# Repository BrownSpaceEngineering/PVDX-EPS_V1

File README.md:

# EPS_V1

Electrical Power System (EPS) for PVDX — battery charging, regulation, and power distribution.

## Status
- Design phase: layout
- Current rev: rev-1.3
- Contributors: Kelly Lin, Natalie Cavallo, Jayla Hsiung, Nick Cavallo, Emily Zhang, Dean Zweiman

## System overview

Four 2S battery packs (8x Tenergy 30005-0 18650 cells) feed a charge/regulation chain built entirely from dedicated power-management ICs, with no onboard MCU — charging, cell balancing, and telemetry are handled in hardware and reported to the compute board over I2C.

**Board sheets:**

- **Battery Pack 1–4**: one **MP2672AGD-0000-Z** charger per pack handles charging, discharging, and cell balancing without needing a microcontroller to manage the process. One **MAX17205** fuel gauge per pack reports state-of-charge and battery telemetry to the compute board over its own I2C pair (SDA/SCL), so each of the 4 packs has an independent data channel — a single fuel-gauge/charger failure doesn't take down monitoring for the other packs.
- **Charging Inputs**: the **MP28167GQ-Z** converts solar input down to a fixed 5V for charging. A **TPS2121RUXR** power mux sits between the solar and external-5V inputs and picks whichever is present, prioritizing external input — this is what lets the board charge normally on the bench (external 5V) without needing solar illumination, while still working correctly on orbit.
- **Converters**: three fixed-output regulators step the ~6–8.4V battery bus down to the rails other subsystems actually need: **TPS62133RGTR** (5V), **TPS62132RGTR** (3.3V), and **TPS61088RHLR** (12V boost, needed since 12V is above the battery bus voltage).
- **Connectors**: battery pack I/O, the RBF (remove-before-flight) pin, inhibit switches (mechanically disconnect batteries from load/ground when pressed — a safety requirement, not just a connector), and the ALRT signal and I2C breakout to the compute board.

### Repo layout

```
EPS_V1/
├── EPS_V1.kicad_pro / .kicad_sch / .kicad_pcb / .step
├── fp-lib-table, sym-lib-table
├── schematics/          # sub-sheets
├── libs/
│   ├── footprints.pretty/
│   ├── symbols/
│   └── 3dmodels/
├── spice/
│   ├── sims/
│   └── models/
├── tools/                # SPICE model translator script
└── manufacturing/
    └── rev-<N>_<date>/
        ├── gerbers/
        ├── bom/
        └── plots/
```

**Why 2S battery packs specifically:** 4x 2S (8 cells total) rather than one large pack — this is a mechanical/electrical packing choice under the ISS 80 Wh limit, and it gives pack-level redundancy (a single pack failure doesn't take down the whole EPS). It also matters electrically: a 2S pack has a ~6.0V floor, which the buck converters can cleanly step down to 5V and 3.3V — a single-cell pack's ~3.0V floor wouldn't support that.

## Key design notes

- **Charge voltage 4.2V, typical 3.6V, overdischarge floor raised from the cell's rated 2.75V to 3.0V** — added margin above the cell's absolute minimum.
- **MP2672A output current is being restricted below the MP28167GQ-Z's 3A capability** to stay under the board's actual current requirement (2.52A = 14/5×0.9). Open question below on whether that restriction should assume all 4 packs charging at once.
- **MAX17205's external-thermistor input is intentionally unused** — flight software reads temperature from the analog thermistor connection straight to the compute board instead, not through the fuel gauge.
- **TPS61088 (12V) key values:** 200kHz min switching frequency (840k resistor), 3A current limit (400k), PFM mode (MODE pin floating), R1 502k / R2 56k for 12V output, 2.2µH inductor per TI's recommended table.
- **Thermistor (NXFT15XV103FEAB025):** system draws 0.574mW through it against a 3mW rating — comfortable margin. Rated -40°C to 125°C.

## Simulations
- `spice/sims/` — EPS_U6, U2_EPS, U3_EPS, U6_EPS (regulator sims)
- `spice/models/` — TI PSpice models for TPS61088/TPS62132/TPS62133, both original and LTSpice-collapsed versions
- `tools/` — script + requirements to collapse TI's multi-line `.lib` continuation format into something LTSpice's autogenerator can parse

## Manufacturing history
| Rev | Date | Notes | Location |
|-----|------|-------|----------|
| 1.0 | 5/15/26 | First layout pass | `manufacturing/rev-1.0_2026-05-15/` |
| 1.2 | 8/7/26  | Prepared for schematic submittal | `manufacturing/rev-1.2_2026-08-07/` |
| 1.3 | 8/30/26  | Prepared for fabrication | `manufacturing/rev-1.3_2026-08-30/` |

## Open items / TBD
- S-band kill switch, FSW-configurable — not yet in design
- R_MID value for MP2672A — placeholder 0, needs datasheet-confirmed value (50Ω noted elsewhere from the fuel gauge datasheet — worth reconciling)
- Solar input voltage range (2.8–22V accepted) vs. actual solar board output — needs confirmation
- MP2672A max charge current restriction — should this account for a scenario where one pack is offline/broken?

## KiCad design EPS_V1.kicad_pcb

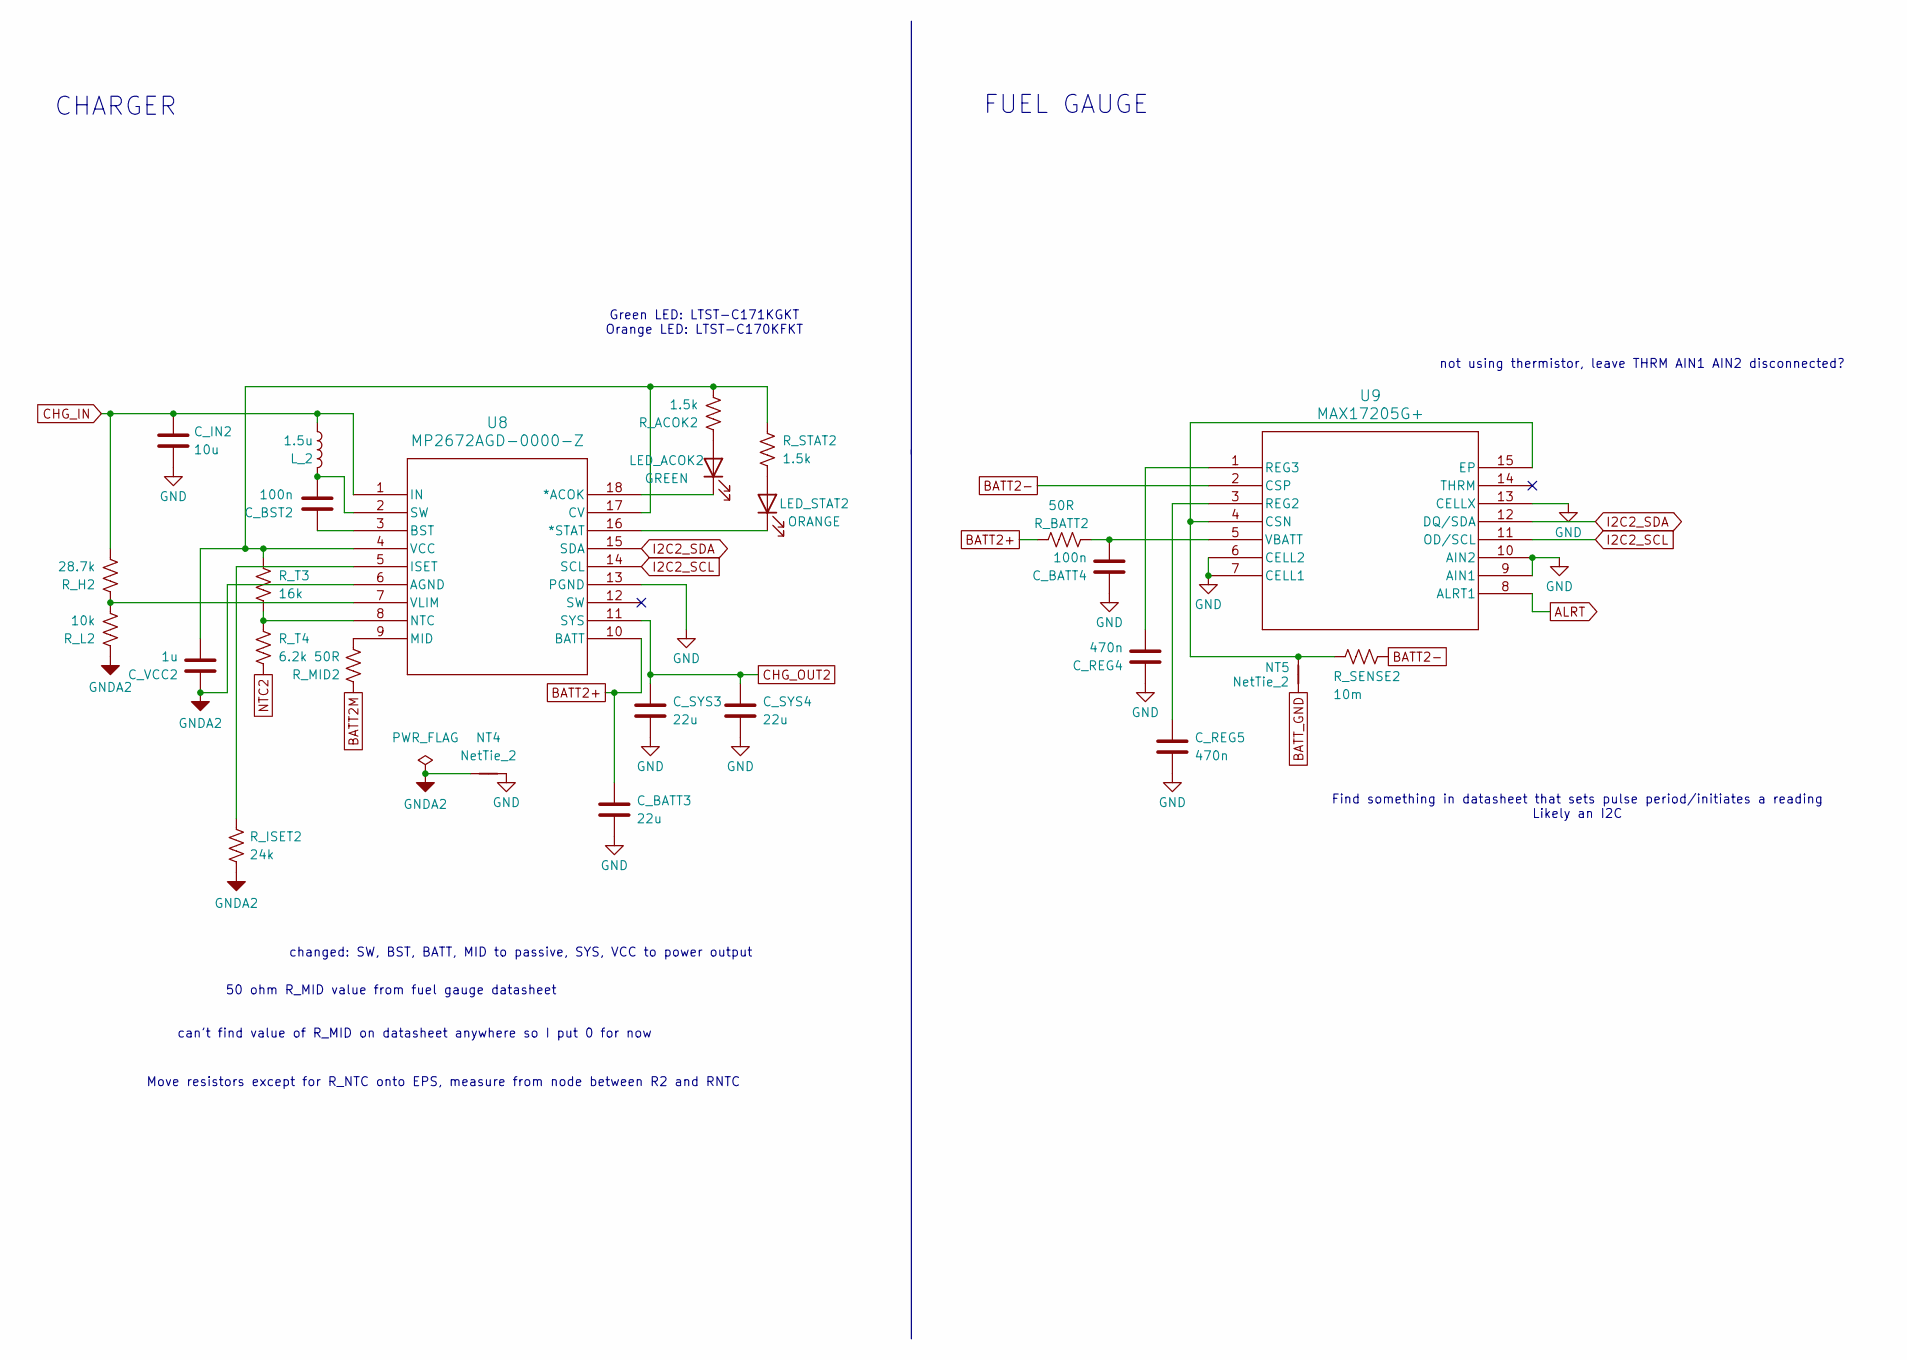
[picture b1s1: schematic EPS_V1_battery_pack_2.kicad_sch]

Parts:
C_BATT3: 22u; C_0805_2012Metric; Voltage Rating 25V
C_BATT4: 100n; C_0603_1608Metric; Voltage Rating 16V
C_BST2: 100n; C_0603_1608Metric; Voltage Rating 16V
C_IN2: 10u; C_0805_2012Metric; Voltage Rating 25V
C_REG4, C_REG5: 470n; C_0603_1608Metric; Voltage Rating 16V
C_SYS3, C_SYS4: 22u; C_0805_2012Metric; Voltage Rating 25V
C_VCC2: 1u; C_0603_1608Metric; Voltage Rating 16V
LED_ACOK2: GREEN; LED_0805_2012Metric; MPN LTST-C171KGKT
LED_STAT2: ORANGE; LED_0805_2012Metric; MPN LTST-C170KFKT
L_2: 1.5u; IND_AMELA2012S-1R5MT; MPN AMELA2012S-1R5MT
NT4, NT5: NetTie_2; NetTie-2_SMD_Pad0.5mm
R_ACOK2: 1.5k; R_0603_1608Metric
R_BATT2: 50R; R_0603_1608Metric
R_H2: 28.7k; R_0603_1608Metric
R_ISET2: 24k; R_0603_1608Metric
R_L2: 10k; R_0603_1608Metric
R_MID2: 50R; R_0603_1608Metric
R_SENSE2: 10m; R_0603_1608Metric
R_STAT2: 1.5k; R_0603_1608Metric
R_T3: 16k; R_0603_1608Metric
R_T4: 6.2k; R_0603_1608Metric
U8: MP2672AGD-0000-Z; QFN-18_MP2672A_MNP
U9: MAX17205G+; 21-0137_T1433&plus_2C_MXM

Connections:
ALRT: U9.8 (ALRT1); also elsewhere on the board
BATT2+: C_BATT3.1, R_BATT2.1, U8.10 (BATT); also elsewhere on the board
BATT2-: R_SENSE2.1, U9.2 (CSP); also elsewhere on the board
BATT2M: R_MID2.1; also elsewhere on the board
BATT_GND: NT5.1; also elsewhere on the board
CHG_IN: C_IN2.1, L_2.1, R_H2.2, U8.1 (IN); also elsewhere on the board
CHG_OUT2: C_SYS3.1, C_SYS4.1, U8.11 (SYS); also elsewhere on the board
GND: C_BATT3.2, C_BATT4.1, C_IN2.2, C_REG4.1, C_REG5.2, C_SYS3.2, C_SYS4.2, NT4.2, U8.13 (PGND), U9.6 (CELL2), U9.7 (CELL1), U9.9 (AIN1), U9.10 (AIN2), U9.13 (CELLX); also elsewhere on the board
GNDA2: C_VCC2.1, NT4.1, R_ISET2.2, R_L2.1, U8.6 (AGND)
I2C2_SCL: U8.14 (SCL), U9.11 (OD/SCL); also elsewhere on the board
I2C2_SDA: U8.15 (SDA), U9.12 (DQ/SDA); also elsewhere on the board
NTC2: R_T4.2; also elsewhere on the board
unnamed: C_BST2.2, L_2.2, U8.2 (SW)
unnamed: LED_ACOK2.2 (A), R_ACOK2.1
unnamed: LED_ACOK2.1 (K), U8.18 (*ACOK)
unnamed: LED_STAT2.2 (A), R_STAT2.2
unnamed: LED_STAT2.1 (K), U8.16 (*STAT)
unnamed: C_BST2.1, U8.3 (BST)
unnamed: C_VCC2.2, R_ACOK2.2, R_STAT2.1, R_T3.1, U8.4 (VCC), U8.17 (CV)
unnamed: R_ISET2.1, U8.5 (ISET)
unnamed: R_MID2.2, U8.9 (MID)
unnamed: R_T3.2, R_T4.1, U8.8 (NTC)
unnamed: R_H2.1, R_L2.2, U8.7 (VLIM)
unnamed: NT5.2, R_SENSE2.2, U9.4 (CSN), U9.15 (EP)
unnamed: C_REG5.1, U9.3 (REG2)
unnamed: C_REG4.2, U9.1 (REG3)
unnamed: C_BATT4.2, R_BATT2.2, U9.5 (VBATT)

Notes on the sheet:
Find something in datasheet that sets pulse period/initiates a reading Likely an I2C
CHARGER
Move resistors except for R_NTC onto EPS, measure from node between R2 and RNTC
50 ohm R_MID value from fuel gauge datasheet
FUEL GAUGE
not using thermistor, leave THRM AIN1 AIN2 disconnected?
can't find value of R_MID on datasheet anywhere so I put 0 for now
Green LED: LTST-C171KGKT Orange LED: LTST-C170KFKT
changed: SW, BST, BATT, MID to passive, SYS, VCC to power output

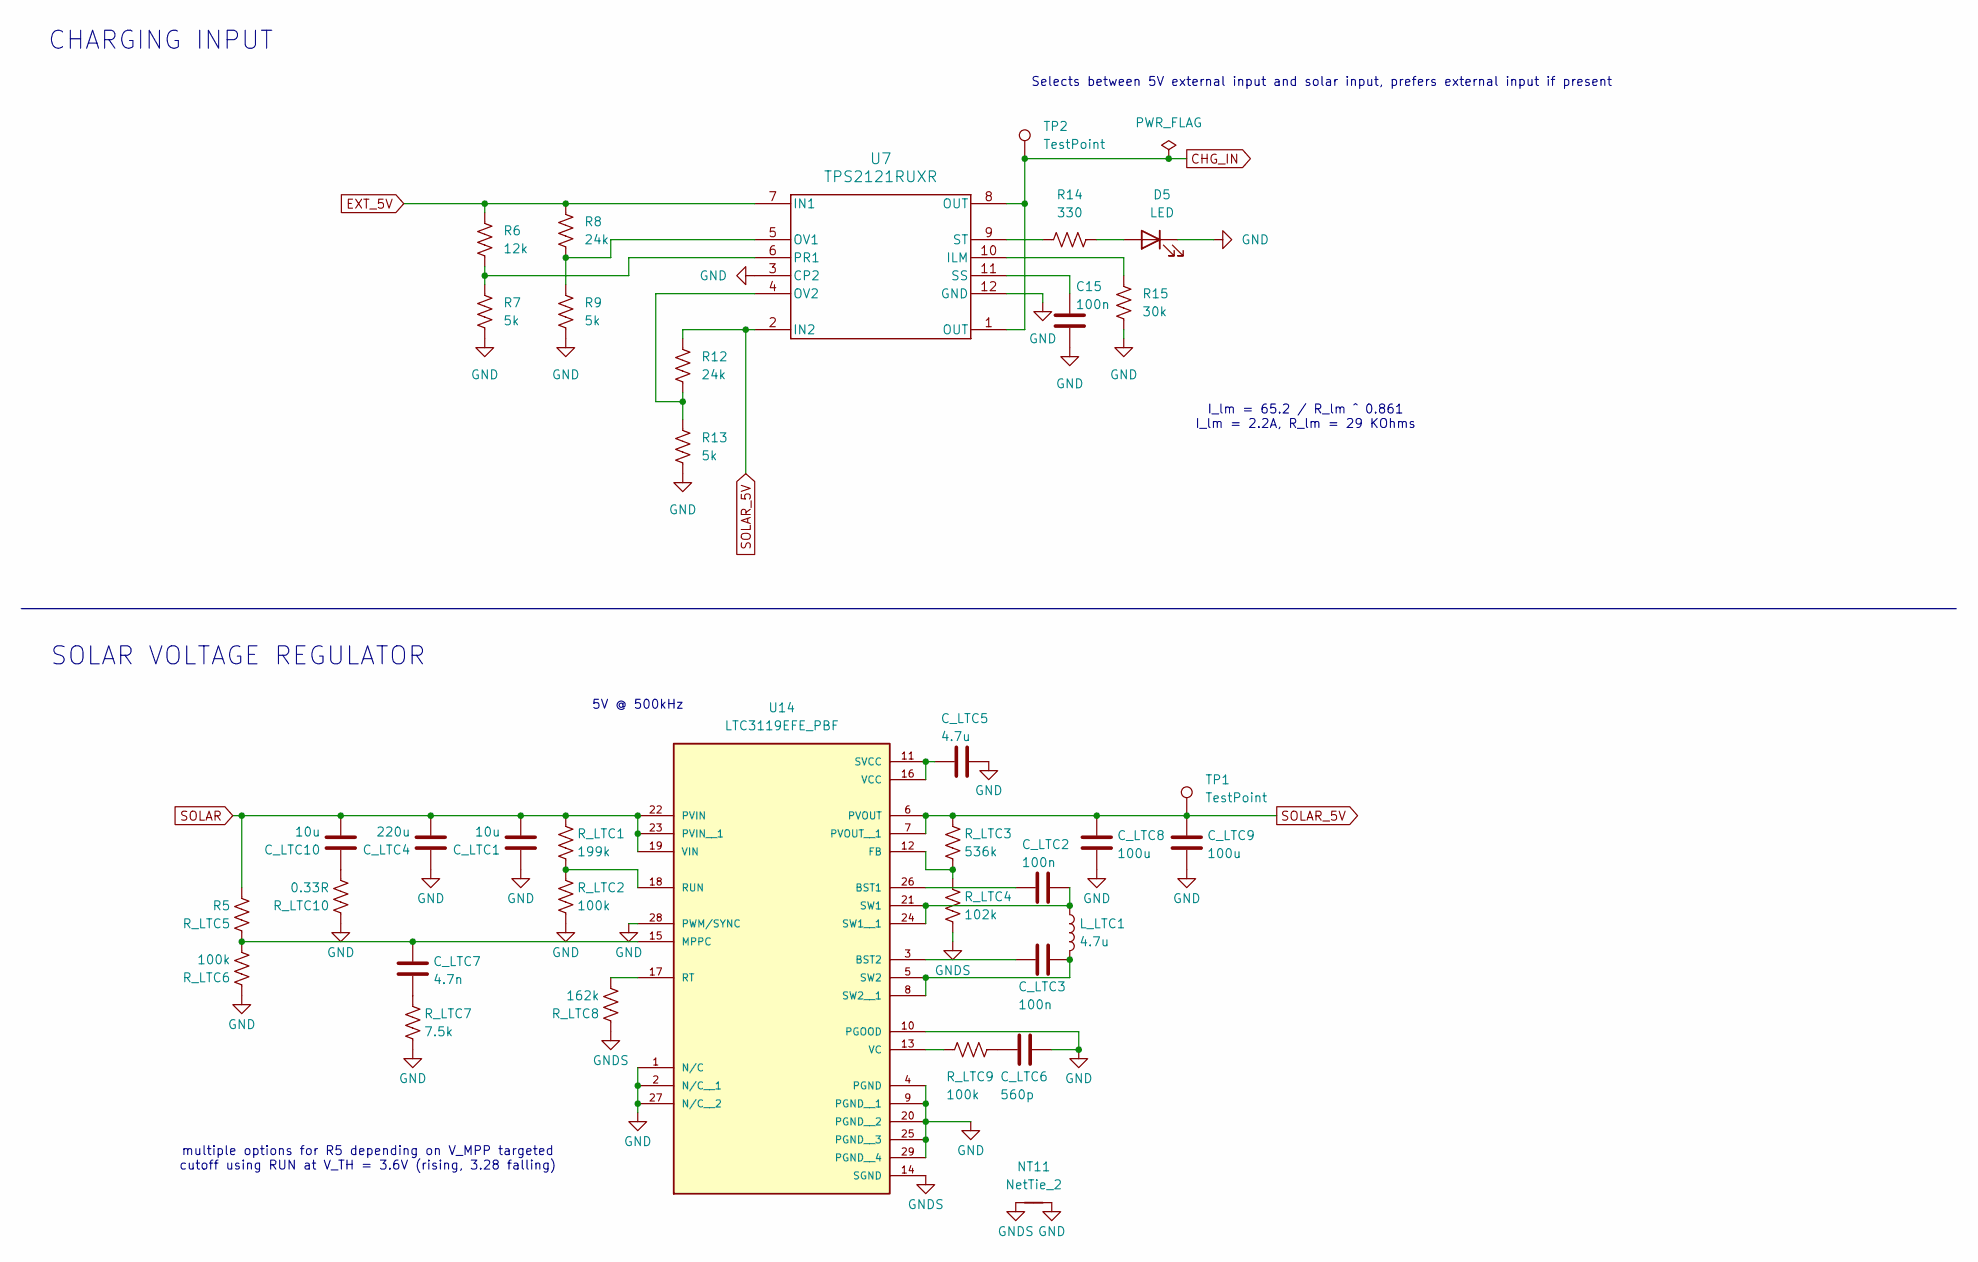
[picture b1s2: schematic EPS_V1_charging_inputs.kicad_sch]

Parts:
C15: 100n; C_0603_1608Metric
C_LTC1, C_LTC10: 10u; C_0805_2012Metric
C_LTC2, C_LTC3: 100n; C_0603_1608Metric
C_LTC4: 220u; CAPMP7.6X4.3_4.3N_KEM
C_LTC5: 4.7u; C_0603_1608Metric
C_LTC6: 560p; C_0603_1608Metric
C_LTC7: 4.7n; C_0603_1608Metric
C_LTC8, C_LTC9: 100u; C_1210_3225Metric
D5: LED; LED_0805_2012Metric
L_LTC1: 4.7u; IND_ASPI-7318-4R7M-T
NT11: NetTie_2; NetTie-2_SMD_Pad0.5mm
R6: 12k; R_0603_1608Metric
R7, R9, R13: 5k; R_0603_1608Metric
R8, R12: 24k; R_0603_1608Metric
R14: 330; R_0603_1608Metric
R15: 30k; R_0603_1608Metric
R_LTC1: 199k; R_0603_1608Metric
R_LTC2, R_LTC6, R_LTC9: 100k; R_0603_1608Metric
R_LTC3: 536k; R_0603_1608Metric
R_LTC4: 102k; R_0603_1608Metric
R_LTC5: R5; R_0603_1608Metric
R_LTC7: 7.5k; R_0603_1608Metric
R_LTC8: 162k; R_0603_1608Metric
R_LTC10: 0.33R; R_0603_1608Metric
TP1, TP2: TestPoint; TestPoint_Pad_D1.5mm
U7: TPS2121RUXR; RUX0012A
U14: LTC3119EFE_PBF; SOP65P640X120-29N; PARTREV B

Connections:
CHG_IN: TP2.1 (1_1), U7.1 (OUT), U7.8 (OUT); also elsewhere on the board
EXT_5V: R6.2, R8.2, U7.7 (IN1); also elsewhere on the board
GND: C15.2, C_LTC1.2, C_LTC4.2, C_LTC5.1, C_LTC6.1, C_LTC8.1, C_LTC9.1, D5.1 (K), NT11.2, R7.1, R9.1, R13.1, R15.1, R_LTC2.2, R_LTC6.1, R_LTC7.2, R_LTC10.1, U7.3 (CP2), U7.12 (GND), U14.1 (N/C), U14.2 (N/C__1), U14.4 (PGND), U14.9 (PGND__1), U14.10 (PGOOD), U14.20 (PGND__2), U14.25 (PGND__3), U14.27 (N/C__2), U14.28 (PWM/SYNC), U14.29 (PGND__4); also elsewhere on the board
GNDS: NT11.1, R_LTC4.2, R_LTC8.1, U14.14 (SGND)
unnamed: C_LTC6.2, R_LTC9.2
unnamed: C_LTC7.1, R_LTC7.1
unnamed: C_LTC10.2, R_LTC10.2
unnamed: D5.2 (A), R14.1
unnamed: R15.2, U7.10 (ILM)
unnamed: R8.1, R9.2, U7.5 (OV1)
unnamed: R12.1, R13.2, U7.4 (OV2)
unnamed: R6.1, R7.2, U7.6 (PR1)
unnamed: C15.1, U7.11 (SS)
unnamed: R14.2, U7.9 (ST)
unnamed: C_LTC2.2, U14.26 (BST1)
unnamed: C_LTC3.2, U14.3 (BST2)
unnamed: R_LTC3.2, R_LTC4.1, U14.12 (FB)
unnamed: C_LTC7.2, R_LTC5.1, R_LTC6.2, U14.15 (MPPC)
unnamed: R_LTC8.2, U14.17 (RT)
unnamed: R_LTC1.2, R_LTC2.1, U14.18 (RUN)
unnamed: C_LTC5.2, U14.11 (SVCC), U14.16 (VCC)
unnamed: C_LTC2.1, L_LTC1.1, U14.21 (SW1), U14.24 (SW1__1)
unnamed: C_LTC3.1, L_LTC1.2, U14.5 (SW2), U14.8 (SW2__1)
unnamed: R_LTC9.1, U14.13 (VC)
SOLAR: C_LTC1.1, C_LTC4.1, C_LTC10.1, R_LTC1.1, R_LTC5.2, U14.19 (VIN), U14.22 (PVIN), U14.23 (PVIN__1); also elsewhere on the board
SOLAR_5V: C_LTC8.2, C_LTC9.2, R12.2, R_LTC3.1, TP1.1 (1_1), U7.2 (IN2), U14.6 (PVOUT), U14.7 (PVOUT__1)

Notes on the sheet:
5V @ 500kHz
Selects between 5V external input and solar input, prefers external input if present
CHARGING INPUT
multiple options for R5 depending on V_MPP targeted cutoff using RUN at V_TH = 3.6V (rising, 3.28 falling)
SOLAR VOLTAGE REGULATOR
I_lm = 65.2 / R_lm ^ 0.861 I_lm = 2.2A, R_lm = 29 KOhms

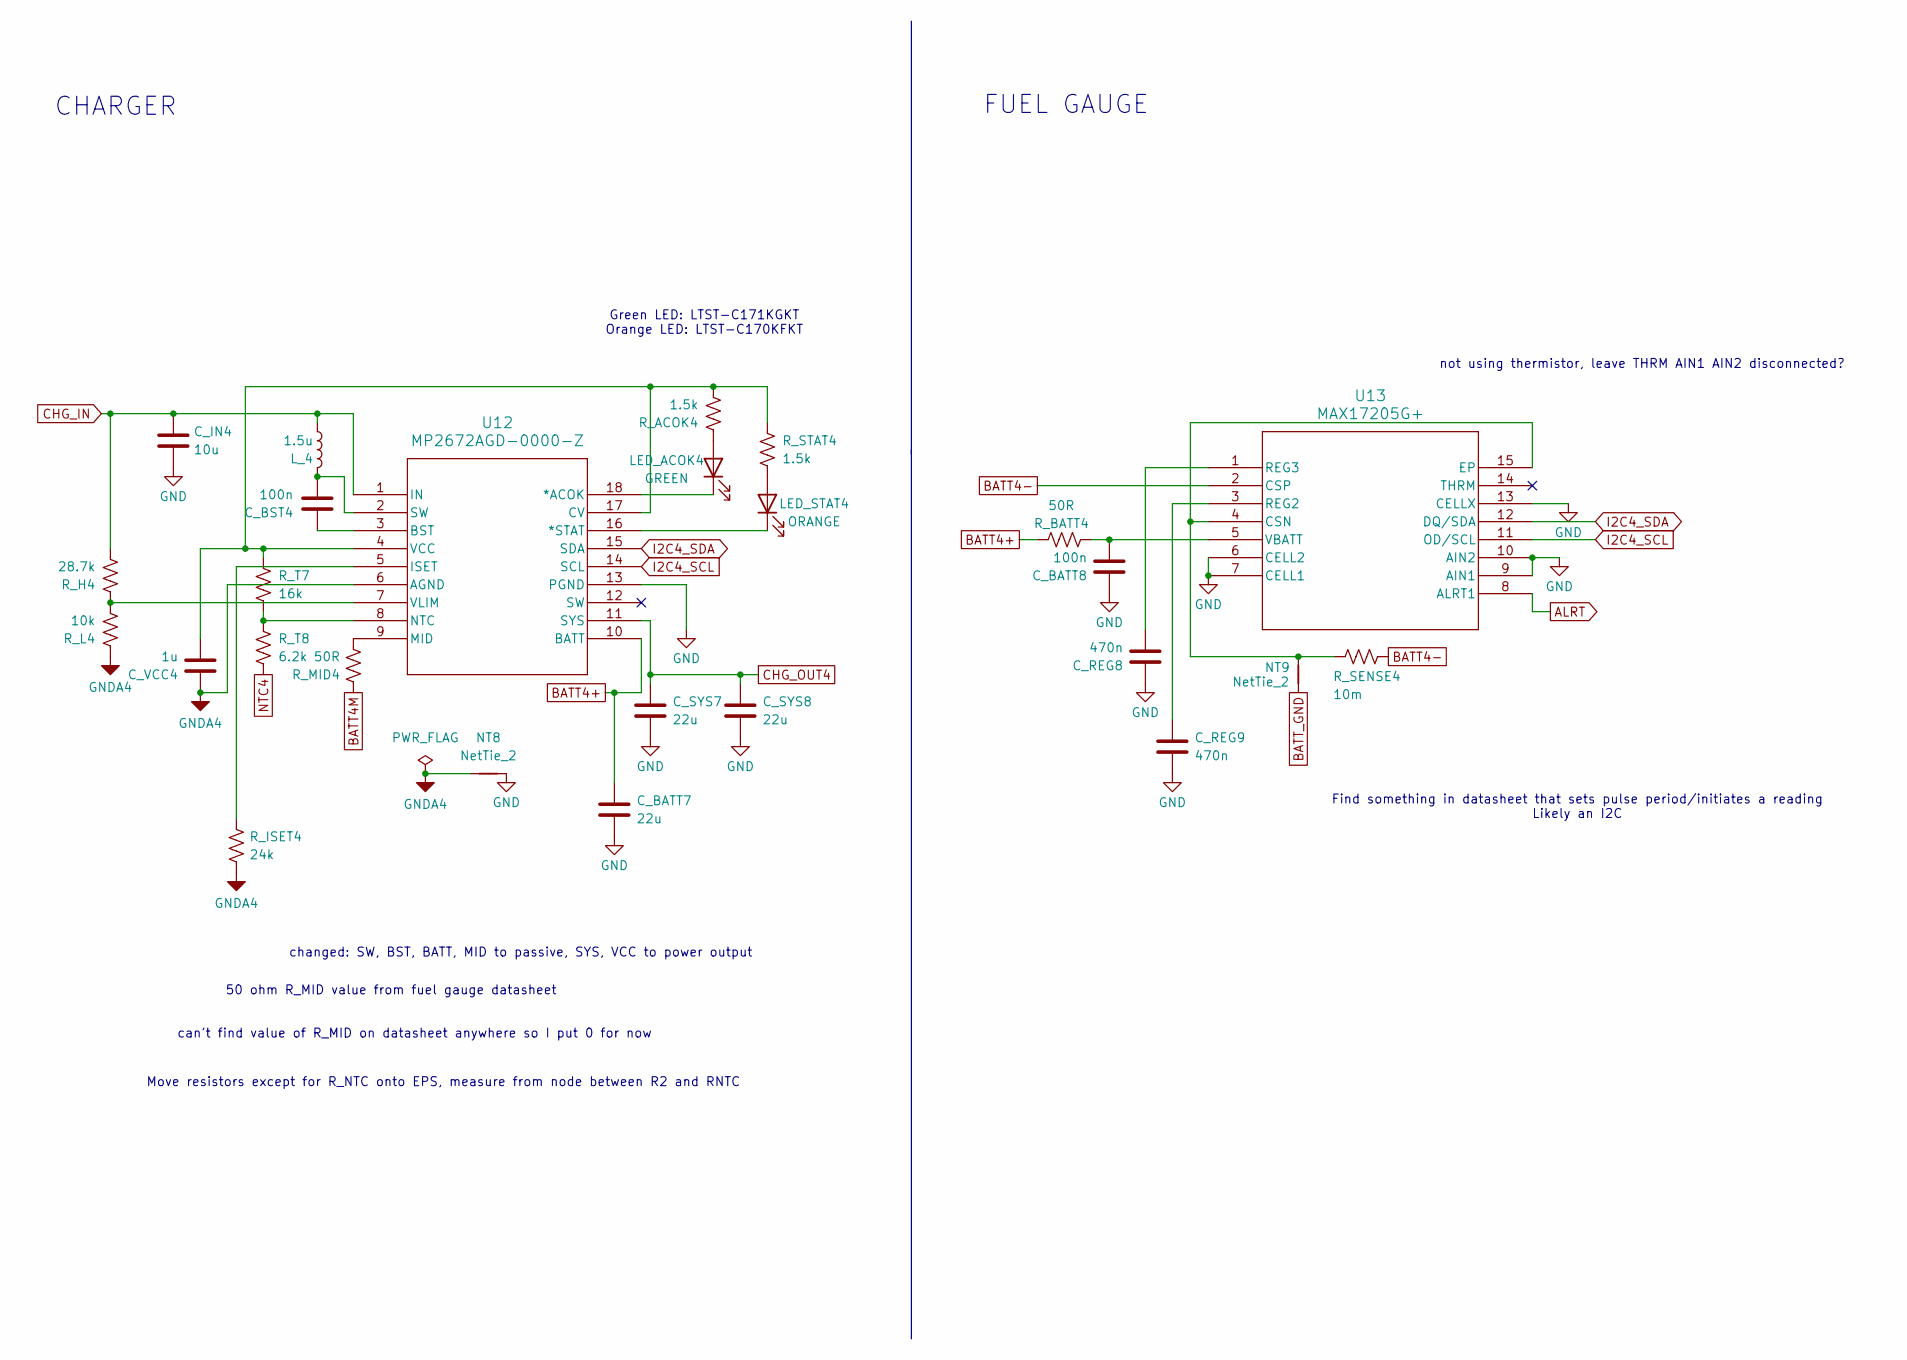
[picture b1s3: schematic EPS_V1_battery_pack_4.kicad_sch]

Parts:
C_BATT7: 22u; C_0805_2012Metric; Voltage Rating 25V
C_BATT8: 100n; C_0603_1608Metric; Voltage Rating 16V
C_BST4: 100n; C_0603_1608Metric; Voltage Rating 16V
C_IN4: 10u; C_0805_2012Metric; Voltage Rating 25V
C_REG8, C_REG9: 470n; C_0603_1608Metric; Voltage Rating 16V
C_SYS7, C_SYS8: 22u; C_0805_2012Metric; Voltage Rating 25V
C_VCC4: 1u; C_0603_1608Metric; Voltage Rating 16V
LED_ACOK4: GREEN; LED_0805_2012Metric; MPN LTST-C171KGKT
LED_STAT4: ORANGE; LED_0805_2012Metric; MPN LTST-C170KFKT
L_4: 1.5u; IND_AMELA2012S-1R5MT; MPN AMELA2012S-1R5MT
NT8, NT9: NetTie_2; NetTie-2_SMD_Pad0.5mm
R_ACOK4: 1.5k; R_0603_1608Metric
R_BATT4: 50R; R_0603_1608Metric
R_H4: 28.7k; R_0603_1608Metric
R_ISET4: 24k; R_0603_1608Metric
R_L4: 10k; R_0603_1608Metric
R_MID4: 50R; R_0603_1608Metric
R_SENSE4: 10m; R_0603_1608Metric
R_STAT4: 1.5k; R_0603_1608Metric
R_T7: 16k; R_0603_1608Metric
R_T8: 6.2k; R_0603_1608Metric
U12: MP2672AGD-0000-Z; QFN-18_MP2672A_MNP
U13: MAX17205G+; 21-0137_T1433&plus_2C_MXM

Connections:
ALRT: U13.8 (ALRT1); also elsewhere on the board
BATT4+: C_BATT7.1, R_BATT4.1, U12.10 (BATT); also elsewhere on the board
BATT4-: R_SENSE4.1, U13.2 (CSP); also elsewhere on the board
BATT4M: R_MID4.1; also elsewhere on the board
BATT_GND: NT9.1; also elsewhere on the board
CHG_IN: C_IN4.1, L_4.1, R_H4.2, U12.1 (IN); also elsewhere on the board
CHG_OUT4: C_SYS7.1, C_SYS8.1, U12.11 (SYS); also elsewhere on the board
GND: C_BATT7.2, C_BATT8.1, C_IN4.2, C_REG8.1, C_REG9.2, C_SYS7.2, C_SYS8.2, NT8.2, U12.13 (PGND), U13.6 (CELL2), U13.7 (CELL1), U13.9 (AIN1), U13.10 (AIN2), U13.13 (CELLX); also elsewhere on the board
GNDA4: C_VCC4.1, NT8.1, R_ISET4.2, R_L4.1, U12.6 (AGND)
I2C4_SCL: U12.14 (SCL), U13.11 (OD/SCL); also elsewhere on the board
I2C4_SDA: U12.15 (SDA), U13.12 (DQ/SDA); also elsewhere on the board
NTC4: R_T8.2; also elsewhere on the board
unnamed: C_BST4.2, L_4.2, U12.2 (SW)
unnamed: LED_ACOK4.2 (A), R_ACOK4.1
unnamed: LED_ACOK4.1 (K), U12.18 (*ACOK)
unnamed: LED_STAT4.2 (A), R_STAT4.2
unnamed: LED_STAT4.1 (K), U12.16 (*STAT)
unnamed: C_BST4.1, U12.3 (BST)
unnamed: C_VCC4.2, R_ACOK4.2, R_STAT4.1, R_T7.1, U12.4 (VCC), U12.17 (CV)
unnamed: R_ISET4.1, U12.5 (ISET)
unnamed: R_MID4.2, U12.9 (MID)
unnamed: R_T7.2, R_T8.1, U12.8 (NTC)
unnamed: R_H4.1, R_L4.2, U12.7 (VLIM)
unnamed: NT9.2, R_SENSE4.2, U13.4 (CSN), U13.15 (EP)
unnamed: C_REG9.1, U13.3 (REG2)
unnamed: C_REG8.2, U13.1 (REG3)
unnamed: C_BATT8.2, R_BATT4.2, U13.5 (VBATT)

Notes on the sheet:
CHARGER
50 ohm R_MID value from fuel gauge datasheet
Green LED: LTST-C171KGKT Orange LED: LTST-C170KFKT
Move resistors except for R_NTC onto EPS, measure from node between R2 and RNTC
FUEL GAUGE
Find something in datasheet that sets pulse period/initiates a reading Likely an I2C
not using thermistor, leave THRM AIN1 AIN2 disconnected?
can't find value of R_MID on datasheet anywhere so I put 0 for now
changed: SW, BST, BATT, MID to passive, SYS, VCC to power output

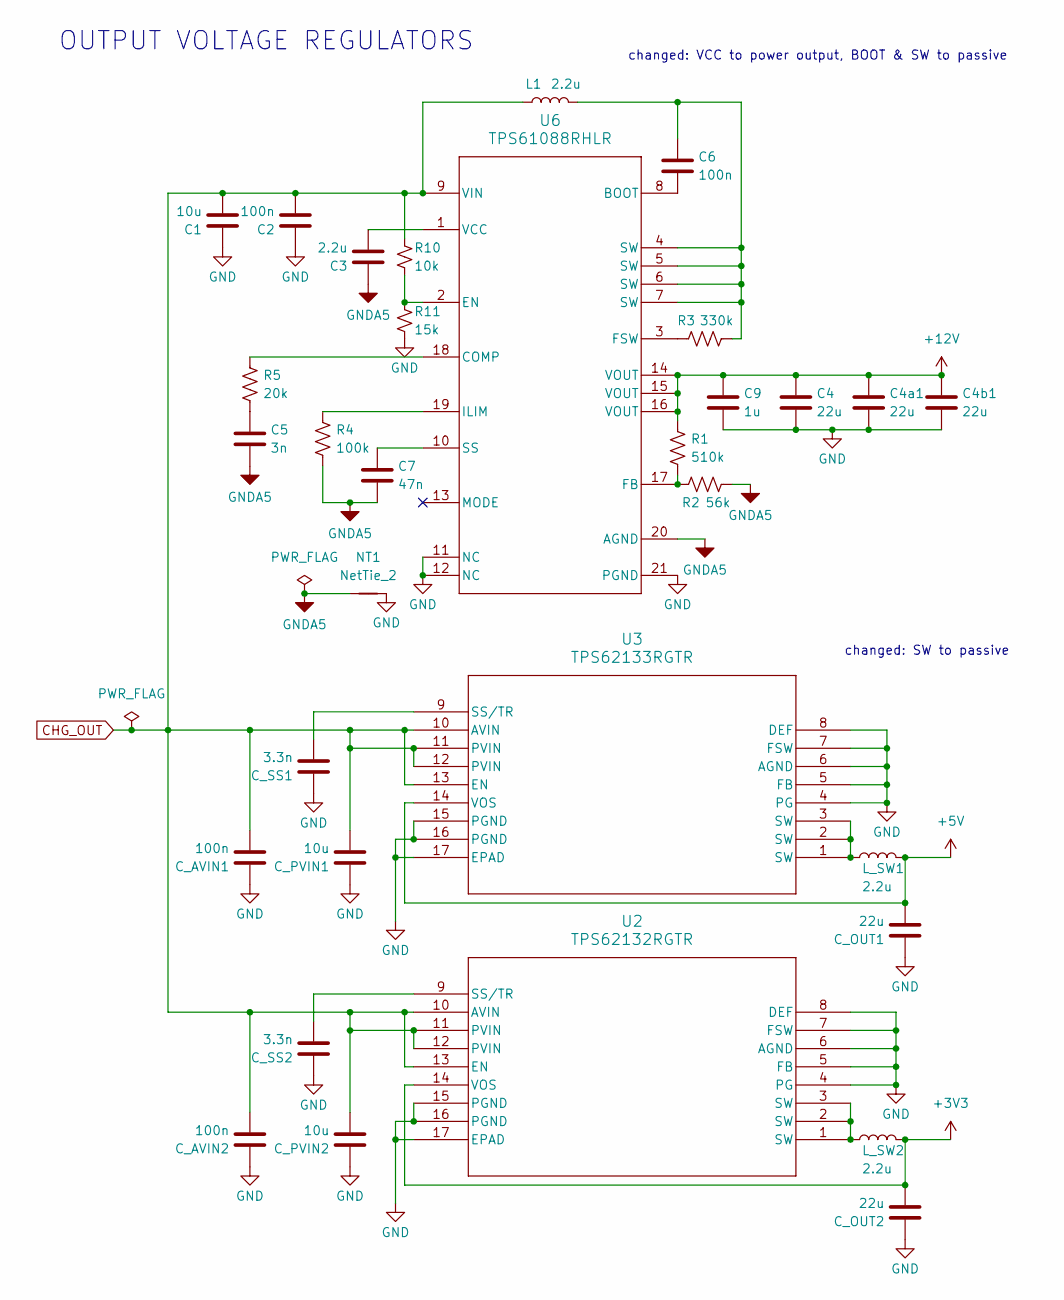
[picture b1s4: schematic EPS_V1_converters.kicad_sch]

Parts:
C1: 10u; C_0805_2012Metric; Voltage Rating 25V
C2, C6: 100n; C_0603_1608Metric; Voltage Rating 16V
C3: 2.2u; C_0603_1608Metric; Voltage Rating 16V
C4, C4a1, C4b1: 22u; C_1206_3216Metric; Voltage Rating 35V
C5: 3n; C_0603_1608Metric; Voltage Rating 10V
C7: 47n; C_0603_1608Metric; Voltage Rating 10V
C9: 1u; C_0603_1608Metric; Voltage Rating 25V
C_AVIN1, C_AVIN2: 100n; C_0603_1608Metric; Voltage Rating 16V
C_OUT1: 22u; C_0805_2012Metric; Voltage Rating 25V
C_OUT2: 22u; C_0805_2012Metric; Voltage Rating 16V
C_PVIN1, C_PVIN2: 10u; C_0805_2012Metric; Voltage Rating 25V
C_SS1, C_SS2: 3.3n; C_0603_1608Metric; Voltage Rating 16V
L1: 2.2u; IND_IFSC_1515AH_VIS; MPN IFSC1515AHER2R2M01
L_SW1, L_SW2: 2.2u; IND_IFSC_1515AH_VIS; MPN IFSC1515AHER2R2M01
NT1: NetTie_2; NetTie-2_SMD_Pad0.5mm
R1: 510k; R_0603_1608Metric
R2: 56k; R_0603_1608Metric
R3: 330k; R_0603_1608Metric
R4: 100k; R_0603_1608Metric
R5: 20k; R_0603_1608Metric
R10: 10k; R_0603_1608Metric
R11: 15k; R_0603_1608Metric
U2: TPS62132RGTR; RGT16_1P7X1P7
U3: TPS62133RGTR; RGT0016C
U6: TPS61088RHLR; RHL0020A

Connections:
+3V3: C_OUT2.2, L_SW2.2, U2.14 (VOS); also elsewhere on the board
+5V: C_OUT1.2, L_SW1.2, U3.14 (VOS); also elsewhere on the board
+12V: C4.1, C4a1.1, C4b1.1, C9.1, R1.1, U6.14 (VOUT), U6.15 (VOUT), U6.16 (VOUT); also elsewhere on the board
CHG_OUT: C1.2, C2.2, C_AVIN1.2, C_AVIN2.2, C_PVIN1.2, C_PVIN2.2, L1.1, R10.1, U2.10 (AVIN), U2.11 (PVIN), U2.12 (PVIN), U2.13 (EN), U3.10 (AVIN), U3.11 (PVIN), U3.12 (PVIN), U3.13 (EN), U6.9 (VIN); also elsewhere on the board
GND: C1.1, C2.1, C4.2, C4a1.2, C4b1.2, C9.2, C_AVIN1.1, C_AVIN2.1, C_OUT1.1, C_OUT2.1, C_PVIN1.1, C_PVIN2.1, C_SS1.1, C_SS2.1, NT1.2, R11.2, U2.4 (PG), U2.5 (FB), U2.6 (AGND), U2.7 (FSW), U2.8 (DEF), U2.15 (PGND), U2.16 (PGND), U2.17 (EPAD), U2.V, U3.4 (PG), U3.5 (FB), U3.6 (AGND), U3.7 (FSW), U3.8 (DEF), U3.15 (PGND), U3.16 (PGND), U3.17 (EPAD), U3.18, U3.19, U3.20, U3.21, U3.22, U6.11 (NC), U6.12 (NC), U6.21 (PGND); also elsewhere on the board
GNDA5: C3.1, C5.2, C7.2, NT1.1, R2.1, R4.2, U6.20 (AGND)
unnamed: C5.1, R5.2
unnamed: C6.1, L1.2, R3.2, U6.4 (SW), U6.5 (SW), U6.6 (SW), U6.7 (SW)
unnamed: L_SW1.1, U3.1 (SW), U3.2 (SW), U3.3 (SW)
unnamed: L_SW2.1, U2.1 (SW), U2.2 (SW), U2.3 (SW)
unnamed: C_SS2.2, U2.9 (SS/TR)
unnamed: C_SS1.2, U3.9 (SS/TR)
unnamed: C6.2, U6.8 (BOOT)
unnamed: R5.1, U6.18 (COMP)
unnamed: R10.2, R11.1, U6.2 (EN)
unnamed: R1.2, R2.2, U6.17 (FB)
unnamed: R3.1, U6.3 (FSW)
unnamed: R4.1, U6.19 (ILIM)
unnamed: C7.1, U6.10 (SS)
unnamed: C3.2, U6.1 (VCC)

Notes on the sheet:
OUTPUT VOLTAGE REGULATORS
changed: VCC to power output, BOOT & SW to passive
changed: SW to passive

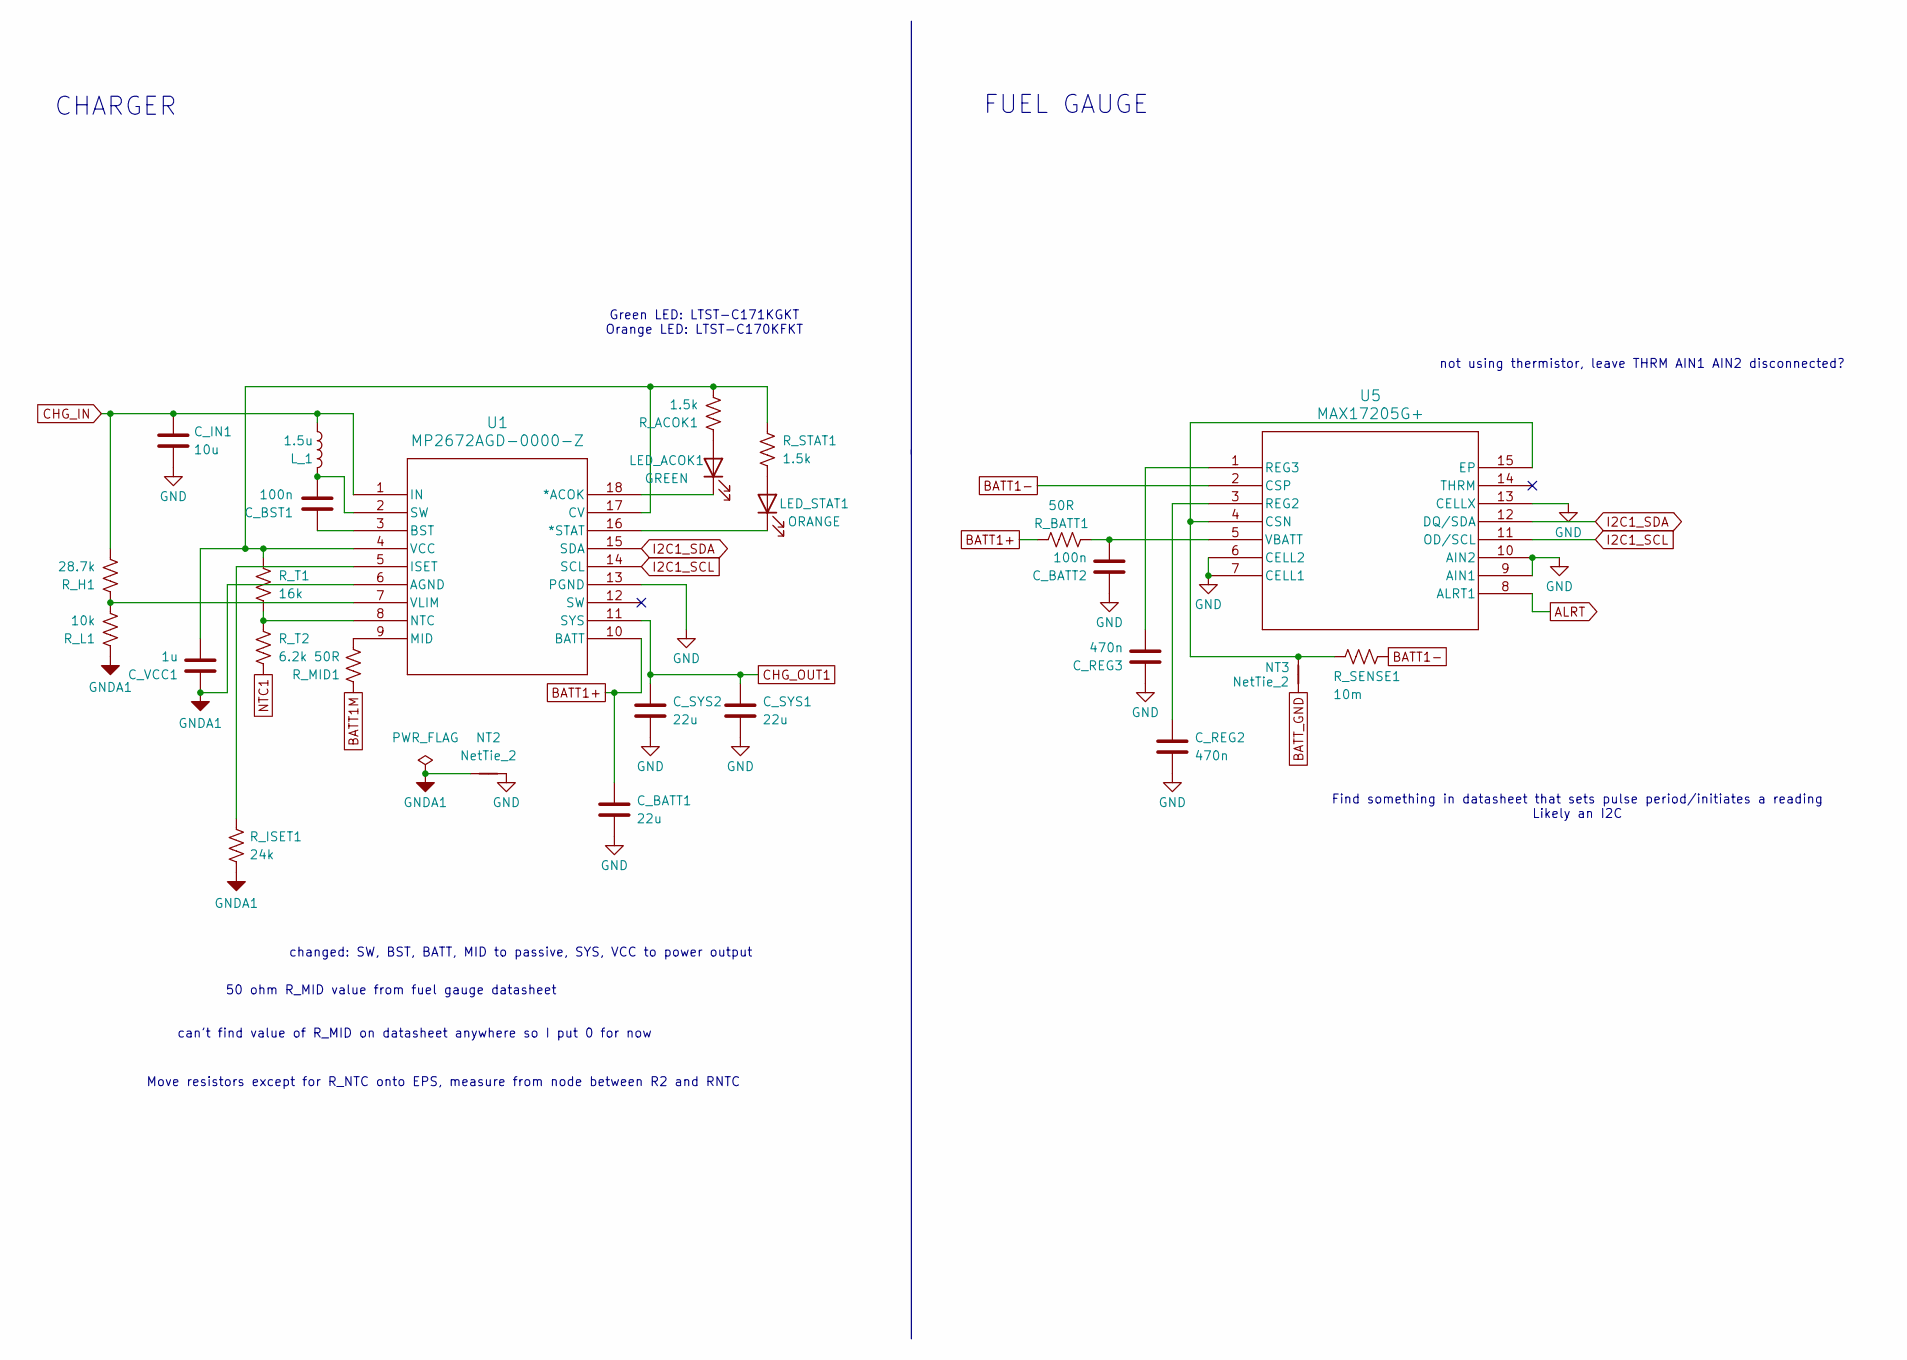
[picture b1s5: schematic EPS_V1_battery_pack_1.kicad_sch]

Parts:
C_BATT1: 22u; C_0805_2012Metric; Voltage Rating 25V
C_BATT2: 100n; C_0603_1608Metric; Voltage Rating 16V
C_BST1: 100n; C_0603_1608Metric; Voltage Rating 16V
C_IN1: 10u; C_0805_2012Metric; Voltage Rating 25V
C_REG2, C_REG3: 470n; C_0603_1608Metric; Voltage Rating 16V
C_SYS1, C_SYS2: 22u; C_0805_2012Metric; Voltage Rating 25V
C_VCC1: 1u; C_0603_1608Metric; Voltage Rating 16V
LED_ACOK1: GREEN; LED_0805_2012Metric; MPN LTST-C171KGKT
LED_STAT1: ORANGE; LED_0805_2012Metric; MPN LTST-C170KFKT
L_1: 1.5u; IND_AMELA2012S-1R5MT; MPN AMELA2012S-1R5MT
NT2, NT3: NetTie_2; NetTie-2_SMD_Pad0.5mm
R_ACOK1: 1.5k; R_0603_1608Metric
R_BATT1: 50R; R_0603_1608Metric
R_H1: 28.7k; R_0603_1608Metric
R_ISET1: 24k; R_0603_1608Metric
R_L1: 10k; R_0603_1608Metric
R_MID1: 50R; R_0603_1608Metric
R_SENSE1: 10m; R_0603_1608Metric
R_STAT1: 1.5k; R_0603_1608Metric
R_T1: 16k; R_0603_1608Metric
R_T2: 6.2k; R_0603_1608Metric
U1: MP2672AGD-0000-Z; QFN-18_MP2672A_MNP
U5: MAX17205G+; 21-0137_T1433&plus_2C_MXM

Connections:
ALRT: U5.8 (ALRT1); also elsewhere on the board
BATT1+: C_BATT1.1, R_BATT1.1, U1.10 (BATT); also elsewhere on the board
BATT1-: R_SENSE1.1, U5.2 (CSP); also elsewhere on the board
BATT1M: R_MID1.1; also elsewhere on the board
BATT_GND: NT3.1; also elsewhere on the board
CHG_IN: C_IN1.1, L_1.1, R_H1.2, U1.1 (IN); also elsewhere on the board
CHG_OUT1: C_SYS1.1, C_SYS2.1, U1.11 (SYS); also elsewhere on the board
GND: C_BATT1.2, C_BATT2.1, C_IN1.2, C_REG2.2, C_REG3.1, C_SYS1.2, C_SYS2.2, NT2.2, U1.13 (PGND), U5.6 (CELL2), U5.7 (CELL1), U5.9 (AIN1), U5.10 (AIN2), U5.13 (CELLX); also elsewhere on the board
GNDA1: C_VCC1.1, NT2.1, R_ISET1.2, R_L1.1, U1.6 (AGND)
I2C1_SCL: U1.14 (SCL), U5.11 (OD/SCL); also elsewhere on the board
I2C1_SDA: U1.15 (SDA), U5.12 (DQ/SDA); also elsewhere on the board
NTC1: R_T2.2; also elsewhere on the board
unnamed: C_BST1.2, L_1.2, U1.2 (SW)
unnamed: LED_ACOK1.2 (A), R_ACOK1.1
unnamed: LED_ACOK1.1 (K), U1.18 (*ACOK)
unnamed: LED_STAT1.2 (A), R_STAT1.2
unnamed: LED_STAT1.1 (K), U1.16 (*STAT)
unnamed: C_BST1.1, U1.3 (BST)
unnamed: C_VCC1.2, R_ACOK1.2, R_STAT1.1, R_T1.1, U1.4 (VCC), U1.17 (CV)
unnamed: R_ISET1.1, U1.5 (ISET)
unnamed: R_MID1.2, U1.9 (MID)
unnamed: R_T1.2, R_T2.1, U1.8 (NTC)
unnamed: R_H1.1, R_L1.2, U1.7 (VLIM)
unnamed: NT3.2, R_SENSE1.2, U5.4 (CSN), U5.15 (EP)
unnamed: C_REG2.1, U5.3 (REG2)
unnamed: C_REG3.2, U5.1 (REG3)
unnamed: C_BATT2.2, R_BATT1.2, U5.5 (VBATT)

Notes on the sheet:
changed: SW, BST, BATT, MID to passive, SYS, VCC to power output
FUEL GAUGE
can't find value of R_MID on datasheet anywhere so I put 0 for now
CHARGER
50 ohm R_MID value from fuel gauge datasheet
Move resistors except for R_NTC onto EPS, measure from node between R2 and RNTC
not using thermistor, leave THRM AIN1 AIN2 disconnected?
Find something in datasheet that sets pulse period/initiates a reading Likely an I2C
Green LED: LTST-C171KGKT Orange LED: LTST-C170KFKT
